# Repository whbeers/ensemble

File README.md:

# Ensemble Fuzz Effect

This is a semi-original octave fuzz, based most directly on the Death By Audio "Octave Clang", but with many of my own tweaks and additions. Designed in [KiCAD](https://www.kicad.org).

The board is built on the ["Noise Floor"](https://github.com/whbeers/noise_floor) pedal platform, which provides basic power protection, audio IO, and a footswitch with LED indicator.

[Schematic PDF](schematics/ensemble-latest.pdf)

## Credit
I drew inspiration from a number of publicly-available octave fuzz schematics, but most directly public traces of the out-of-production [Death By Audio](https://deathbyaudio.com/) "Octave Clang" as portrayed in the PCBGuitarMania ["Death by Octaver" schematic](https://pcbguitarmania.com/product/death-by-octaver/), and by various contributors to the [thread at freestomboxes.org](https://www.freestompboxes.org/viewtopic.php?t=11122). I became interested in the effect after hearing the original maker, Oliver Ackermann, [demonstrate the Octave Clang](https://youtu.be/_RslAoTyIwk?t=2671) in a feature on EarthQuaker Devices' YouTube channel.

Thanks as always to the folks on the [freestompboxes.org](https://www.freestompboxes.org/) forum for feedback and suggestions.

Potentiometer 3D model courtesy [Vasily Kashirin](https://grabcad.com/vasily.kashirin-1).

SPDT toggle switch 3D model courtesy [Stephanie Schwecke](https://grabcad.com/stephanie.schwecke-1).

4PDT toggle switch 3D model courtesy [David Farrow](https://grabcad.com/library/4pdt-toggle-switch-1).

*I am not affiliated with any of the brands, sites, or products named in this overview.*

## My Modifications
Using what I could find out about Octave Clang as a basis, my circuit makes the following modifications:
 - added flexibility through three switchable voices for the octave stage:
   1. primary->secondary, full winding: a subtle driven octave effect
   2. secondary->primary, full winding: a clangorous metallic octave, most similar to the public demos of the Octave Clang
   3. secondary->primary, half winding: an even louder and more overt octave effect, thanks to the higher effective ratio of turns between secondary and primary windings. In this mode the octave effect is evident throughout most of the fretboard.
 - added a balance control to give further flexibility in the level of octave effect vs drive
 - added a (switchable) hard clipping stage to rein in the overall output level and add a very distinct, but still octave fuzz voice to the effect
 - tweaked component values to make the effect slightly more accessible across a range of volumes and gains (and to use more commonly-available values)
 - omitted the input-side tone control pot, as it tended to attenuate the signal to an unhelpful degree

## Versioning

My pcb designs utilize the following versioning scheme (I'll add to this as I produce more revisions):
 - v0.0XX: A candidate design that has not yet been produced and tested.
 - v0.XX: A design that has been produced, tested, and any initial errors addressed.

## Name
*The name "Ensemble" is a reflection of the nature of the effect (a blend of various octave fuzz and drive voices) and [security nerdery](https://www.usenix.org/system/files/sec19-chen-yuanliang.pdf).*

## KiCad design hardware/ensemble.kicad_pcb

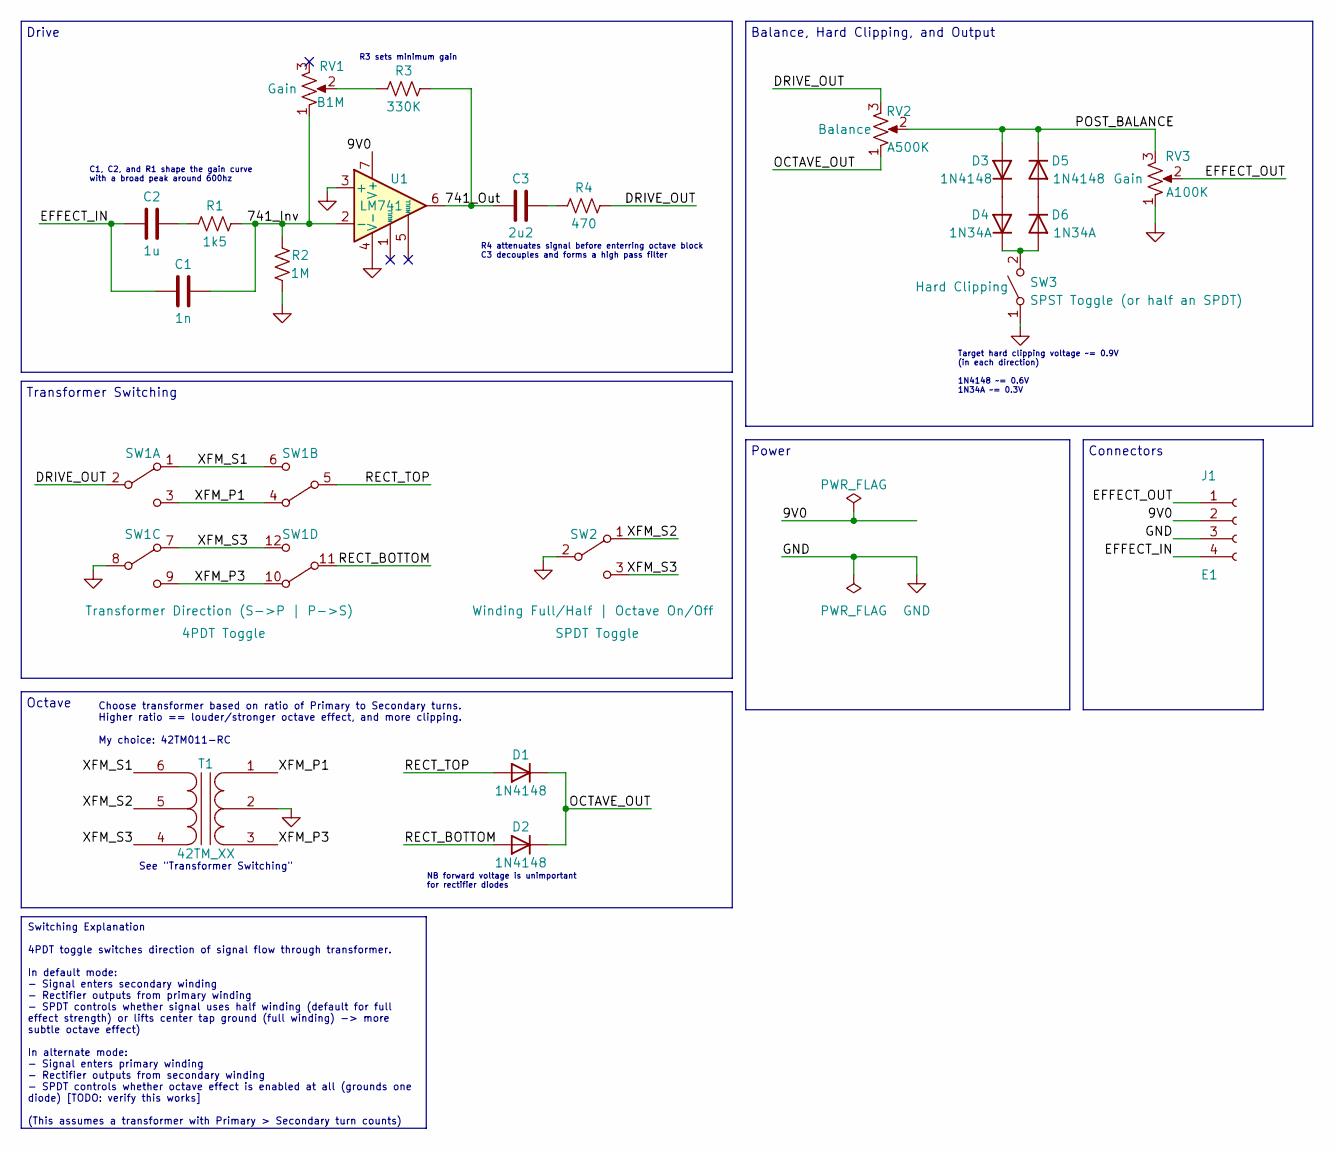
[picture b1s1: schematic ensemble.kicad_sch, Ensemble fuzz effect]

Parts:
C1: 1n; C_Disc_D4.3mm_W1.9mm_P5.00mm
C2: 1u; C_Disc_D4.3mm_W1.9mm_P5.00mm
C3: 2u2; C_Disc_D4.3mm_W1.9mm_P5.00mm
D1, D2, D3, D5: 1N4148; D_DO-35_SOD27_P7.62mm_Horizontal
D4, D6: 1N34A; D_DO-35_SOD27_P7.62mm_Horizontal
J1: E1; Molex_PicoBlade_53047-0410_1x04_P1.25mm_Vertical_with_3D_Mo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
R1: 1k5; R_Axial_DIN0207_L6.3mm_D2.5mm_P7.62mm_Horizontal
R2: 1M; R_Axial_DIN0207_L6.3mm_D2.5mm_P7.62mm_Horizontal
R3: 330K; R_Axial_DIN0207_L6.3mm_D2.5mm_P7.62mm_Horizontal
R4: 470; R_Axial_DIN0207_L6.3mm_D2.5mm_P7.62mm_Horizontal
RV1: B1M; Potentiometer_Single_3_Horizontal
RV2: A500K; Potentiometer_Single_3_Horizontal
RV3: A100K; Potentiometer_Single_3_Horizontal
SW1: 4PDT Toggle; SW_4PDT_SOLDER_LUGS
SW2: SPDT Toggle; SW_SPDT_SOLDER_LUGS
SW3: SPST Toggle (or half an SPDT); SW_SPDT_SOLDER_LUGS
T1: 42TM_XX; Transformer_42TM
U1: LM741; DIP-8_W7.62mm_Socket

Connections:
/9V0: J1.2, U1.7 (V+)
/741_Inv: C1.2, R1.1, R2.2, RV1.1, U1.2 (-)
/741_Out: C3.1, R3.2, U1.6
/DRIVE_OUT: R4.1, RV2.3, SW1.2 (A2)
/EFFECT_IN: C1.1, C2.1, J1.4
/EFFECT_OUT: J1.1, RV3.2
/OCTAVE_OUT: D1.1 (K), D2.1 (K), RV2.1
/POST_BALANCE: D3.2 (A), D5.1 (K), RV2.2, RV3.3
/RECT_BOTTOM: D2.2 (A), SW1.11 (D2)
/RECT_TOP: D1.2 (A), SW1.5 (B2)
/XFM_P1: SW1.3 (A3), SW1.4 (B1), T1.1 (AA)
/XFM_P3: SW1.9 (C3), SW1.10 (D1), T1.3 (AB)
/XFM_S1: SW1.1 (A1), SW1.6 (B3), T1.6 (SB)
/XFM_S2: SW2.1 (A), T1.5 (SC)
/XFM_S3: SW1.7 (C1), SW1.12 (D3), SW2.3 (C), T1.4 (SA)
GND: J1.3, R2.1, RV3.1, SW1.8 (C2), SW2.2 (B), SW3.1 (A), T1.2 (AC), U1.3 (+), U1.4 (V-)
unnamed: C2.2, R1.2
unnamed: C3.2, R4.2
unnamed: D3.1 (K), D4.2 (A)
unnamed: D4.1 (K), D6.2 (A), SW3.2 (B)
unnamed: D5.2 (A), D6.1 (K)
unnamed: R3.1, RV1.2

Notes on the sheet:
Switching Explanation 4PDT toggle switches direction of signal flow through transformer. In default mode: - Signal enters secondary winding - Rectifier outputs from primary winding - SPDT controls whether signal uses half winding (default for full effect strength) or lifts center tap ground (full w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
Transformer Switching
Target hard clipping voltage ~= 0.9V (in each direction) 1N4148 ~= 0.6V 1N34A ~= 0.3V
Choose transformer based on ratio of Primary to Secondary turns. Higher ratio == louder/stronger octave effect, and more clipping. My choice: 42TM011-RC
See "Transformer Switching"
Drive
C1, C2, and R1 shape the gain curve with a broad peak around 600hz
R4 attenuates signal before enterring octave block C3 decouples and forms a high pass filter
Balance, Hard Clipping, and Output
Power
R3 sets minimum gain
NB forward voltage is unimportant for rectifier diodes
Octave
Connectors

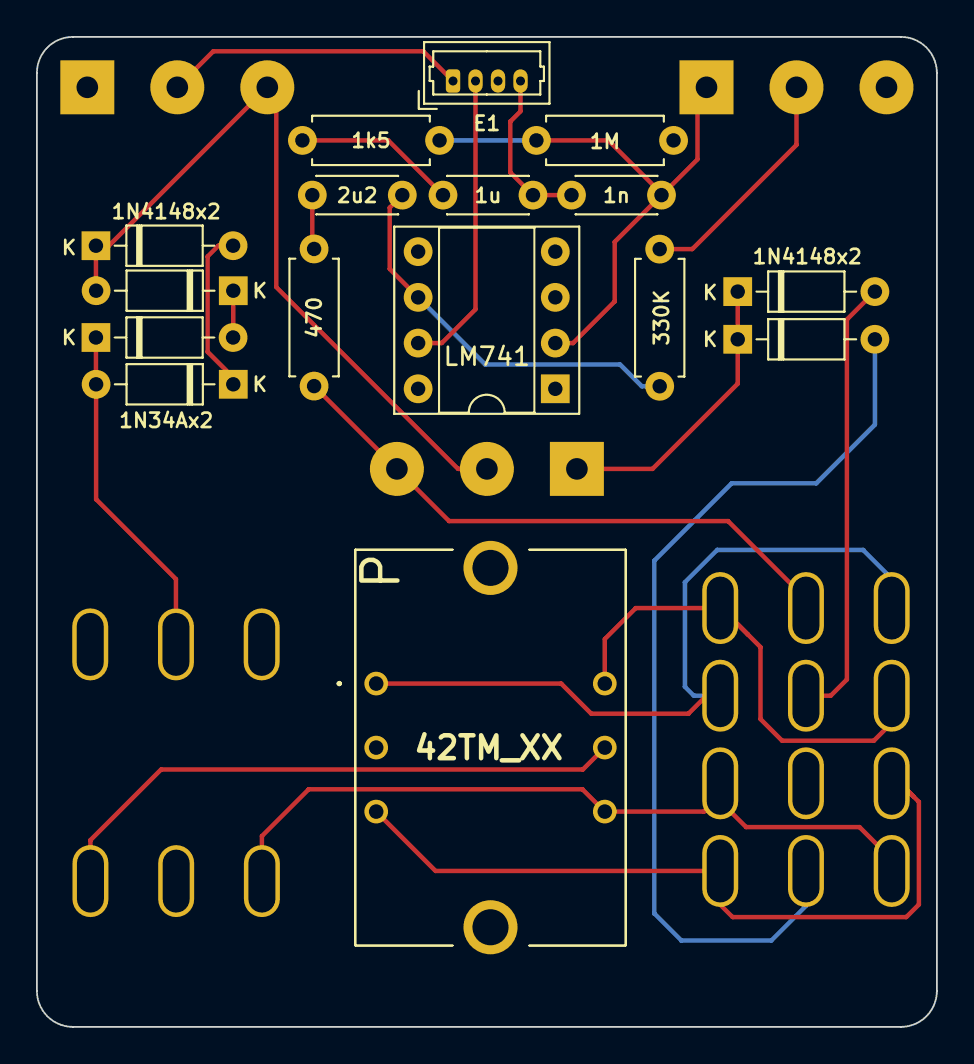
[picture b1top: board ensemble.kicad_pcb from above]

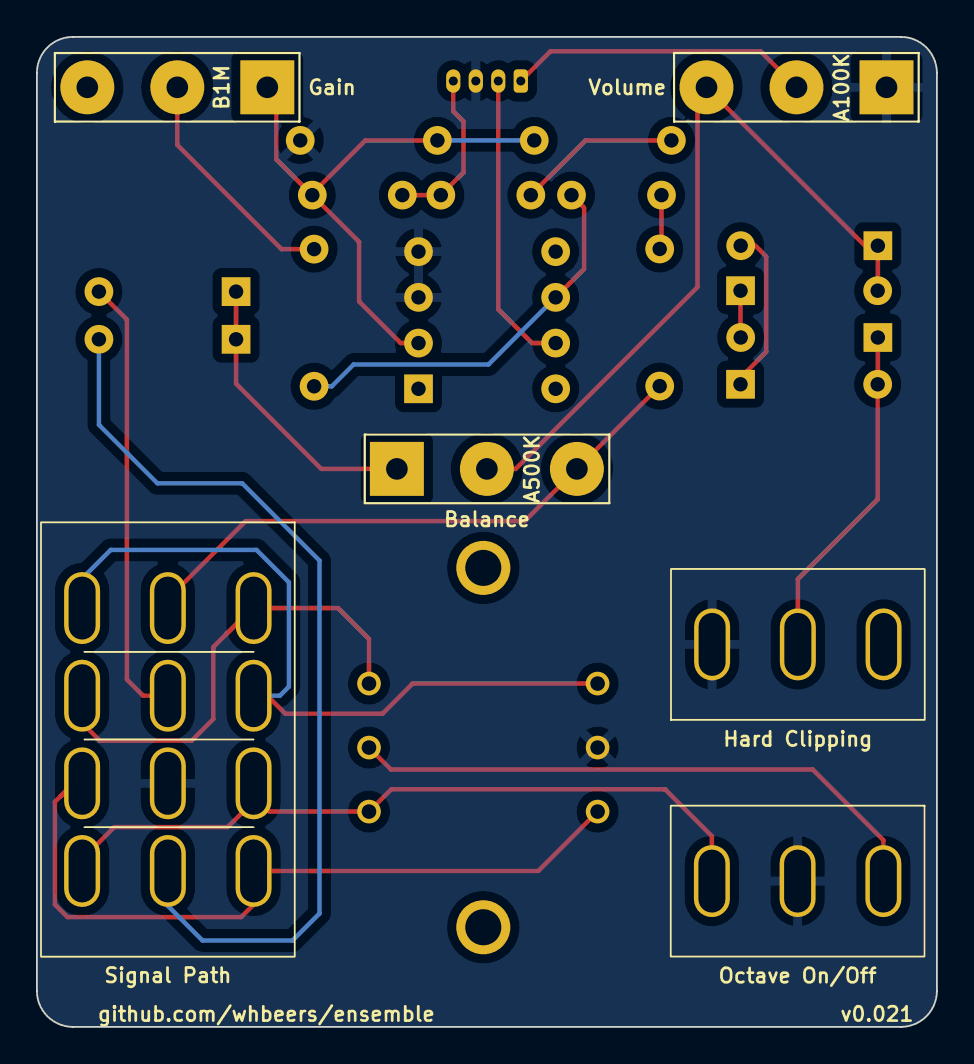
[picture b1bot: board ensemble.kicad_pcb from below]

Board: 2 copper layers, 50.0 x 55.0 mm, 22 parts (6 on the bottom side), 22 nets.

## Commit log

2023-03-17 initial structure and description
2023-03-17 more on the readme
2023-03-17 initial schematic for Ensemble
2023-03-17 fix schematic background
2023-03-18 add footprints and models for all components
2023-03-18 initial layout
2023-03-18 add renders
2023-03-18 add link and revision
2023-03-19 further iteration on layout
2023-03-19 fix 4pdt model alignment and initial routing
2023-03-19 tweak input-side filtering based on simulations, move to correct footprint for caps and diodes.
2023-03-19 slight routing and layout changes
2023-03-19 updated schematic
2023-03-19 one quick routing change
2023-03-19 update renders
2023-03-19 getting closer to happy with the layout
2023-03-27 fix credit for models
2023-03-27 add credit for 4PDT
